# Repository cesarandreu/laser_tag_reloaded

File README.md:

#Laser Tag Reloaded - System

---

##What is this

This is a laser tag system which connects to your android smartphone using bluetooth. Your smartphone then connects to a remote server which handles tracking the lobby and game data. 

The program flow is simple: You pair the smartphone with the gun/vest, you join or create a lobby, and then you play! 

Each player is assigned a number, which gets transmitted by the infrared laser. When another player receives a valid enemy number it transmits this to the smartphone, and then the smartphone transmits it to the server.

When the end game conditions are met, the server nofies every player. At the end of each game you can see a map with markers showing the places where you got shot. 

---

###Project Links

The project has three components: 

* [__System__ (Gun + Vest)](https://github.com/cesarandreu/laser_tag_reloaded)

* [__Server__ (Node.js) ](https://github.com/cesarandreu/laser_tag_nodejs)

* [ __Smartphone application__ (Android)](https://github.com/cesarandreu/laser_tag_android)

Videos

* [System demonstration](http://www.youtube.com/watch?v=hs2FppfotFk)

---

###System

The system (gun + vest) has an infrared laser, two infrared receivers, a speaker, a bluetooth module, a GPS module, a battery gauge, a battery charger, a battery, an LED bar graph, and two push-buttons. 

The essential components are: the infrared laser, the infrared receivers, the speaker, the bluetooth, and the push-button. (And a power source.) These components are required for the system to function. You could remove the LED graph, second button, battery charger, battery gauge, and GPS, and still maintain system functionality. (Although this would require commenting out the appropriate code in _real-main.c_ and _game.c_ in order to prevent any issues.)

Everything is controlled through bluetooth commands. The system changes through different states depending on which command is sent. You can see the bluetooth commands in the _communication.c_ library; you can also see the game code for each command in the _game.c_ library. 

Basically, the system goes into a _Connected_ state when bluetooth communication is established. Then it goes to _New Game_ mode, which initializes all the interrupts, the storage, and the player variables. Afterwards it awaits for the _Game Information_ command which tells it the game type, the game limit, the list of enemy numbers, and your own player number. When it receives the _Game Start_ command it enables the receivers and trigger button. From this point on the game is live, and whenever a shot is received it transmits the number and location data to the smartphone; when the trigger is pressed the infrared laser transmits your player code. When the server decides that the game has ended it informs the smartphone, the smartphone then sends a _Game End_ command, which resets all the variables, sends everything that is in storage, and disables the receivers and trigger. 

At this point you could start a new game from the smartphone, and the whole process would be repeated.

---

####Picture of the system

This is a picture of the final gun. We purchased this toy gun and modded it to put the board and all the components inside. It connects to a vest through a phone cable. 

---

####Building your own

If you wish to build your own you can find the schematic inside the _Other_ folder. You can also find a list of all the components in our report.

Once you've put the system together you'll have to configure the [command-line toolchain](http://leaflabs.com/docs/unix-toolchain.html). It's only tested on the [maple mini](http://leaflabs.com/docs/hardware/maple-mini.html), but it should work on the maple if you update _initialize.c_ accordingly. 

After that you should be able to clone this repository and run `make`, and then `make install`. 

__WARNING:__ You can take a look at the `Tests` folder for some of the tests we used, or to get an idea of how some of the code works. However, we haven't updated all the files inside, so some may be outdated. Use them at your own risk.

---

####More Information

Inside the _Other_ folder you can find the report that we prepared for our professor. In there you can find information on the components, power analysis, timing analysis, and an in-depth description of the whole system. Pretty much all the information is there. We've included the schematics as well.

There's also a folder with a PCB that we designed. However, we were unable to print and test it. If you decide to print the PCB you'll have to wirewrap two sections in order to ensure uniform ground. We recommend wire-wrapping the ground plane that contains the SDA and SCL pins of the battery monitor to the ground plane containing the Trigger button, and from there, wire-wrap to any other ground-plane in order to ensure uniform ground potential.

If you have any questions feel free to contact us, or just raise an issue. We'll be glad to help if we can.

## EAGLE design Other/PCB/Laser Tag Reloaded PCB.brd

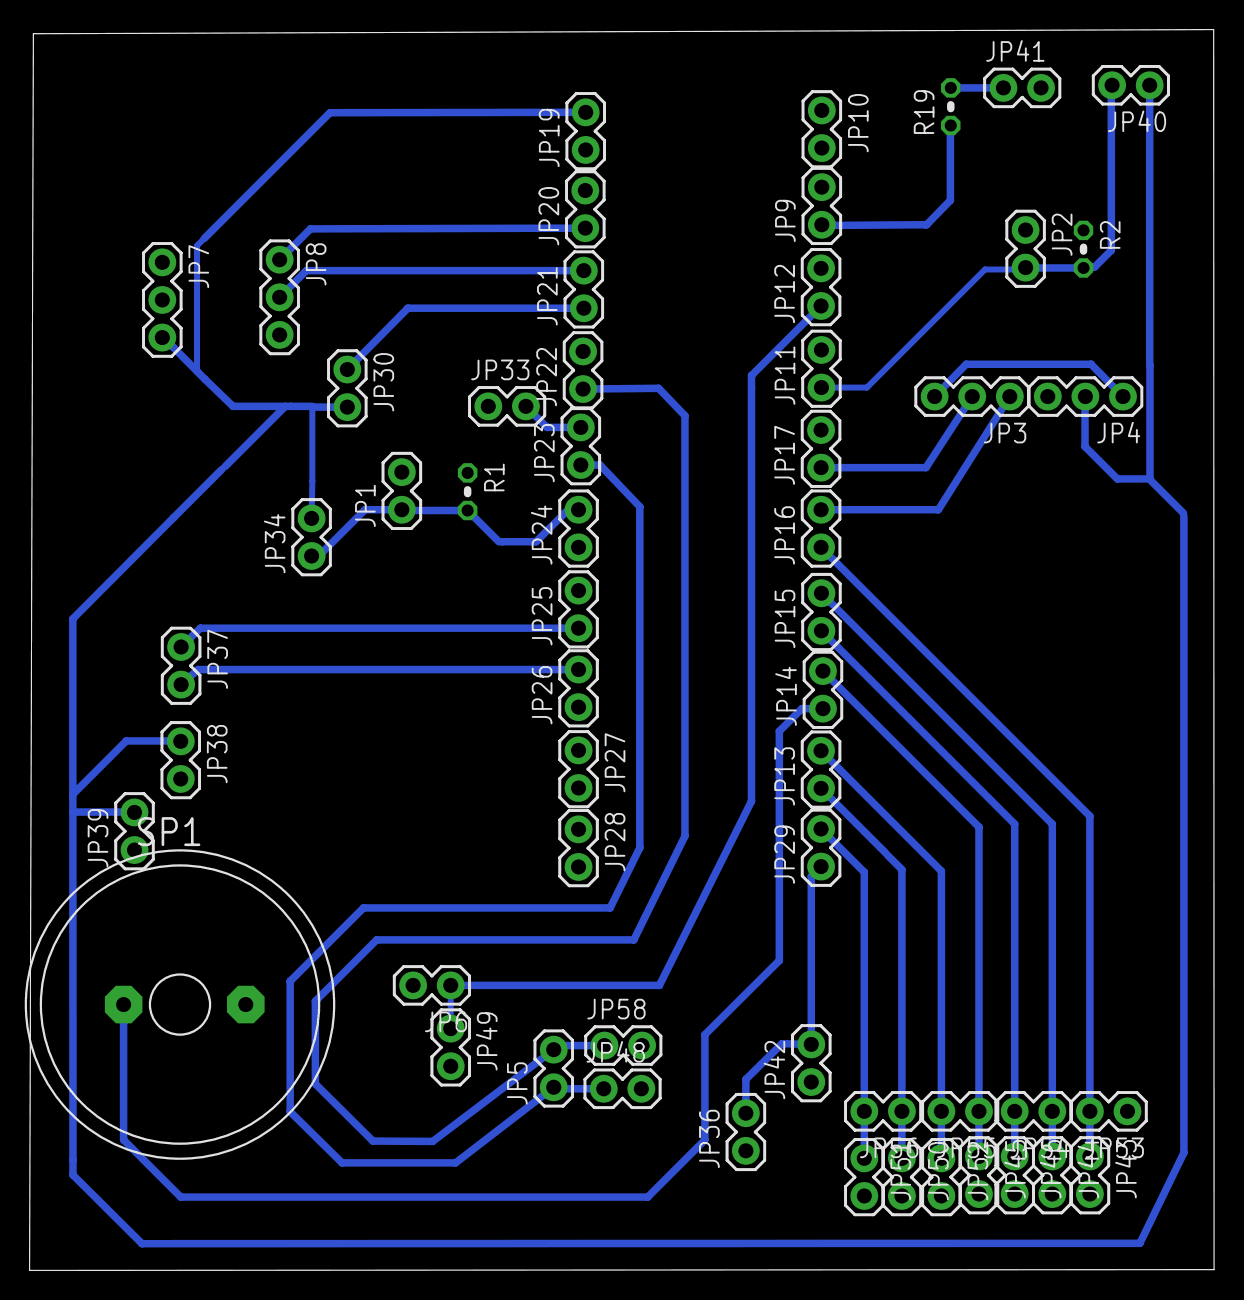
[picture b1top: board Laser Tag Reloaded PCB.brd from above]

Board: 2 copper layers, 80.0 x 83.8 mm, 56 parts (0 on the bottom side), 26 nets.

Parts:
JP1, JP2, JP5, JP6, JP9, JP10, JP11, JP12, JP13, JP14, JP15, JP16, JP17, JP19, JP20, JP21, JP22, JP23, JP24, JP25, JP26, JP27, JP28, JP29, JP30, JP33, JP34, JP36, JP37, JP38, JP39, JP40, JP41, JP42, JP43, JP44, JP45, JP46, JP48, JP49, JP50, JP51, JP52, JP53, JP54, JP55, JP56, JP58: 1X02
JP3, JP4, JP7, JP8: 1X03
R1, R2: 1k; 0204V
R19: 10; 0204V
SP1: AL201P

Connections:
GND: JP1.2, JP2.1, JP4.3, JP6.2, JP7.2, JP8.3, JP33.1, JP36.1, JP38.2, JP41.2, JP42.1, JP43.2, JP44.2, JP45.2, JP46.2, JP48.2, JP49.2, JP50.2, JP51.2, JP52.2, JP53.1, JP58.2, R1.1, R2.1, SP1.2
unnamed: JP1.1, JP24.2, JP34.1, R1.2
unnamed: JP3.3, JP4.1
unnamed: JP5.2, JP22.1, JP58.1
unnamed: JP21.1, JP30.1
unnamed: JP23.2, JP33.2
unnamed: JP41.1, R19.2
unnamed: JP2.2, JP11.1, JP40.2, R2.2
unnamed: JP5.1, JP23.1, JP48.1
unnamed: JP25.1, JP37.1
unnamed: JP26.2, JP37.2
unnamed: JP8.1, JP20.1
unnamed: JP9.1, R19.1
unnamed: JP8.2, JP21.2
unnamed: JP6.1, JP12.1, JP49.1
unnamed: JP14.1, SP1.1
unnamed: JP3.2, JP17.1
unnamed: JP3.1, JP16.2
unnamed: JP16.1, JP43.1, JP53.2
unnamed: JP15.2, JP44.1, JP54.1
unnamed: JP15.1, JP46.1, JP54.2
unnamed: JP14.2, JP45.1, JP55.1
unnamed: JP13.2, JP52.1, JP55.2
unnamed: JP13.1, JP50.1, JP56.1
unnamed: JP29.2, JP51.1, JP56.2
VCC: JP4.2, JP7.3, JP19.2, JP29.1, JP30.2, JP34.2, JP36.2, JP38.1, JP39.2, JP40.1, JP42.2

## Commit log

2013-04-08 Added USB library, Initialization library. Updated gitignore.
2013-04-08 Added bluetooth library and started adding tests.
2013-04-08 Fixed bluetooth library. Added bluetooth and usb tests.
2013-04-08 Updated bluetooth with some printing functions.
2013-04-08 Updated README. Added TODO to some files. Added speaker. Added two speaker tests.
2013-04-09 Added IR sender. Added some more tests.
2013-04-09 Adding GPS header, C implementation, and test code. Also adding i2c headers and implementations.
2013-04-09 Added receiver.
2013-04-09 Adding Fuel Gauge test code and updating GPS Implementation.
2013-04-09 Fixed rules and main and receiver.
2013-04-11 Slight changes. Removed main.cpp which did nothing. Fixed real-main.c.
2013-04-11 Updated .gitignore to ignore real-main.c
2013-04-11 Committing GPS hasFix corrections and adding check for fix in gps_test.
2013-04-11 Removing real-main.c to comply with new .gitignore.
2013-04-14 Adding fuelGauge headers and implementation.
    Updating GPS headers and implementation.
    Updating fuelGauge test to match new header.
    Updating rules.mk to include fuelGauge header.
2013-04-14 Added Player lib. Updates Sender and Receiver a bit.
2013-04-15 Update receiver.c
    added a return to listenForIR that if currentPulse >5 return 0
2013-04-15 Update receiver.c
    Added a few functions at the end. Added a few define variables for good measure. Adjusted the MAXPULSES devided by 8 of the original. Added a voidFuncPtr but I have no idea what I was doing with that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
2013-04-16 Fixed warning-related issues in fuelGauge.c and GPS.c
2013-04-16 Working on fixing receiver and speaker issues.
2013-04-16 Working on fixing the receiver. When you press the pushbutton it'll trigger the receiver interrupt.
2013-04-17 Removed a line.
2013-04-18 Updated bluetooth so that all the defines are in the header. Updates player so that the shots fired cannot pass one million. Added communication library which can properly parse received information!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
2013-04-18 Added communication test.
2013-04-18 Added New Game function.
2013-04-20 Added enemy library. Commented out tests in communication.c. Added enemy to rules.
2013-04-20 Updated communication with a few comments.
2013-04-20 Added enemy library and storage library. Added both to rules.
2013-04-20 Updated storage so that it returns the number it deleted when it removes something. Otherwise it returns zero. Updated communication with some transmit functions! And added the responses that the MCU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
2013-04-20 Fixed communication.c, it was printing the game type without quotation marks. Added communicationResponseTransmit_Test. It works with all the commands from what I can tell.
2013-04-20 Added an extra escape condition to communication.
2013-04-20 Committing changes to reciever.c minor changes to GPS.c.
2013-04-20 IT COMPILES. Yay! Added game library. It handles the game logic. Well, it handles the state changes in the system. Added function calls to game library from communication. Modified receiver library s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
    On a personal note: I feel like a badass right now. I feel like today I've made a lot of progress! :D
2013-04-20 I forgot to actually uncomment the game library function calls in communication. Fixed it now.
2013-04-22 Moved some of the game related logic to game.c, it was originally in communication.c. Now the enemies are put in an array and then they're added to the enemy library from game.c. Added some defines t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
    communication.c specific:
    Updated one of the responses so that now it sends the player number.
    Added some safety escape condition to getNext.
    Added a bit of documentation on top of each different type of parsing function.
    Added some minimum/maximum length exit conditions to these parsing functions.
    Created a resetBuffer f
2013-04-22 Added some testing code to game.c that should be removed later.
2013-04-22 Made the player library use signed integers for the shot counter. Increased the maximum number of hits to 128 in the storage library. Made game over response respond with the response number. Fixed a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
2013-04-22 Added timer to GPS implementation to wait for fix.
    GPS coordinate string size corrected.
    Added USART buffer clearing in relevant functions.
    Also added a small comment in receiver.c and removed some old test code.
2013-04-22 Updated the strings that are sent to the phone so that they can be parsed right away with the JSONObject class on Android. That way we can pass the objects directly to the JavaScript.
2013-04-23 Fixed gps_hasFix blocking and some other minor hiccups.
    Added trigger.h and trigger.c to handle trigger enable/disable and
    interrupt enabling/disabling.
2013-04-23 Testing GPS.
2013-04-25 Added connection check as one of the valid messages that the MCU can receive.
2013-04-26 Mother forgive me.
    Basically bailed on low-power on GPS for the time being, it will go
    into low-power tracking though.
    Fixed gauge_voltage in gauge implementation.
    Added some minor test code to receiver to confirm interrupt operation.
    Back receiver code has been (sloppily) implemented, need to fix some
    variable names.
2013-04-26 Revert "Mother forgive me."
    This reverts commit d4830611953393f11a79fd042305f8f1bce3d851.
2013-04-26 Cleanup and fixes.
    Cleaned up the tests a bit to use implementation functions and some
    filing.
2013-05-01 Small changes to storage and game to make it slightly more robust in case of magical failure.
2013-05-02 Committing some ledGraph and fuelGauge fixes, as well as a GPS rewrite.
    GPS rewrite still in progress and rather ugly.
2013-05-02 Commented out some stuff.
2013-05-02 Adding necessary header to ledGraph.h
2013-05-02 Added default interrupt to trigger as a placeholder for initialization.
2013-05-02 Removed a playSound in receivers. Updating Game.C library.
2013-05-02 Updated Game.C. Fixed a small bug in trigger.c, where the function pointer wasn't initialized.
2013-05-02 Moved game headers to Game.h from Game.c.
2013-05-02 No newline at end of file.
2013-05-02 Fixed some errors that didn't let it compile.
2013-05-03 Added gps trigger interrupt functions. Set the speaker to turn on GPS interrupts during playback. Changed some variable initializations in the GPS code. Increased LED Graph for 5 seconds.
2013-05-03 Fixed a bug in communicaton. Added some interrupt disablers. Made some variables volatile.
2013-05-08 Adding delay.h and delay.c to simulate invulnerability periods when shot.
2013-05-08 Updating fuelGauge.c to time out when i2c query takes too long.
    -May require testing to confirm it doesn't always timeout.
2013-05-09 Added some tests.
2013-05-09 Game Delays and Minor Fixes
    -Added trigger delay to prevent "automatic firing"
    -Added 5 second invulnerability timer when a receiver is hit.
    -Added delay testers.
    -Updated game.c with the relevant functions to include delay
    considerations.
2013-05-09 Modified storage so that it returns the hit it saved. And made a few variables volatile just in case.
2013-05-09 Some game modification that I'm gonna fix in a bit.
2013-05-09 Fixed game lib enabling proper gps and receiver functions. Removed redundant comments.
2013-05-09 DO NOT USE THIS CODE. IT FUCKS UP.
2013-05-10 This version is working with Receiver, Sender, Speaker, and Bluetooth.
2013-05-10 Slowly incrementing versions. This has working trigger and working receiver. Tested working.
2013-05-10 Both receivers are tested working.
2013-05-10 Currently working! Moved includes from game.c to game.h Increased storage size from 128 to 256 Made it so that storage_add returns the hit it added Renamed trigger function names Set some communicati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
2013-05-10 The delay when you are hit is working. It lasts five seconds.
2013-05-10 Forgot to add the delay in the rules.
2013-05-10 Fixed trigger interrupt.
2013-05-10 Added LED Graph code. When you press the button it gets the battery percentage.
2013-05-10 Added trigger delay! It waits 125ms to let you shoot again. It is tested working!
2013-05-10 GPS has been added. It appears to work. Not fully tested. May blow up.
2013-05-10 Adding Untested Code
    Switch to master for tested code
2013-05-10 Real main added. This is what compiles.
2013-05-14 Added fullGame test to test the game.
2013-05-16 Added schematic, updating README.
2013-05-16 Small fix in README.
2013-05-16 Added schematics, PCB, report and image. Updated README.
2013-05-16 Fixed image link.
2013-05-16 Added youtube link. Picture of system.

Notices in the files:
parts and their libraries:
SparkFun-Connectors: Licensing: CC v3.0 Share-Alike You are welcome to use this library for commercial purposes.
